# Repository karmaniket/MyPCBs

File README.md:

<h1 align="center">Explore my PCBs!!</h1>
<table>
  <tr>
    <td>
      <h3 align="center">Ldr sensor</h3>
      
    </td>
    <td>
      <h3 align="center">flip flop Led</h3>
      
    </td>
  </tr>
</table>

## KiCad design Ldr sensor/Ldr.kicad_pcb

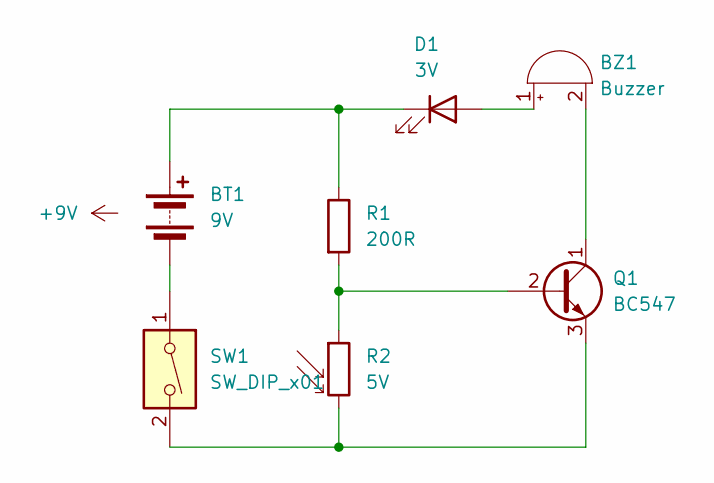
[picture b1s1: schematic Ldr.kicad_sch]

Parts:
BT1: 9V; Battery_connector
BZ1: Buzzer; Buzzer_12x9.5RM7.6
D1: 3V; LED_0805_2012Metric_Pad1.15x1.40mm_HandSolder
Q1: BC547; TO-92_Inline
R1: 200R; R_0805_2012Metric_Pad1.20x1.40mm_HandSolder
R2: 5V; R_LDR_10x8.5mm_P7.6mm_Vertical
SW1: SW_DIP_x01; SW_DIP_SPSTx01_Slide_6.7x4.1mm_W8.61mm_P2.54mm_LowProfile

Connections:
unnamed: BT1.1 (+), D1.1 (K), R1.1
unnamed: BT1.2 (-), SW1.1
unnamed: BZ1.2 (+), Q1.1 (C)
unnamed: BZ1.1 (-), D1.2 (A)
unnamed: Q1.2 (B), R1.2, R2.1
unnamed: Q1.3 (E), R2.2, SW1.2

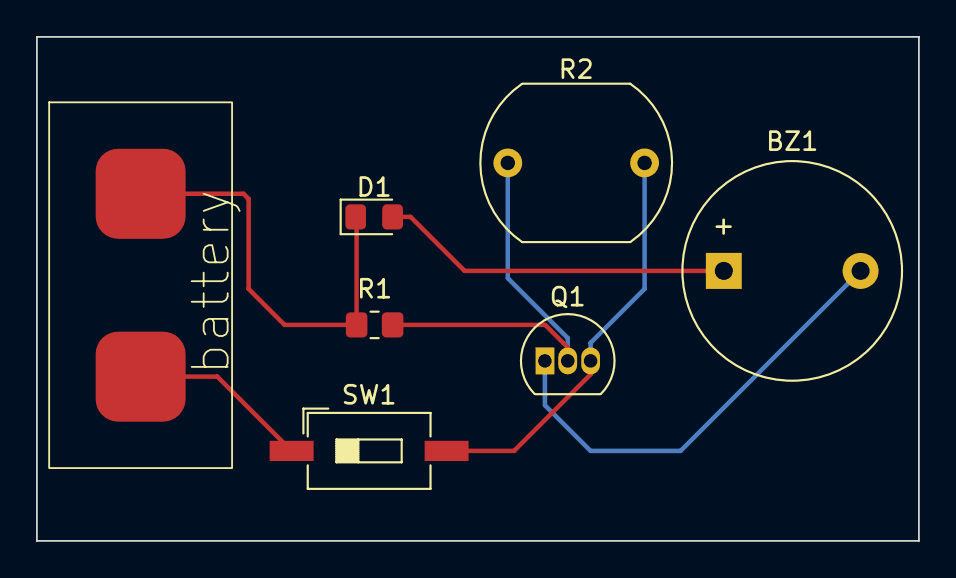
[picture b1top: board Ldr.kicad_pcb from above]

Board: 2 copper layers, 49.0 x 28.0 mm, 7 parts (0 on the bottom side), 6 nets.

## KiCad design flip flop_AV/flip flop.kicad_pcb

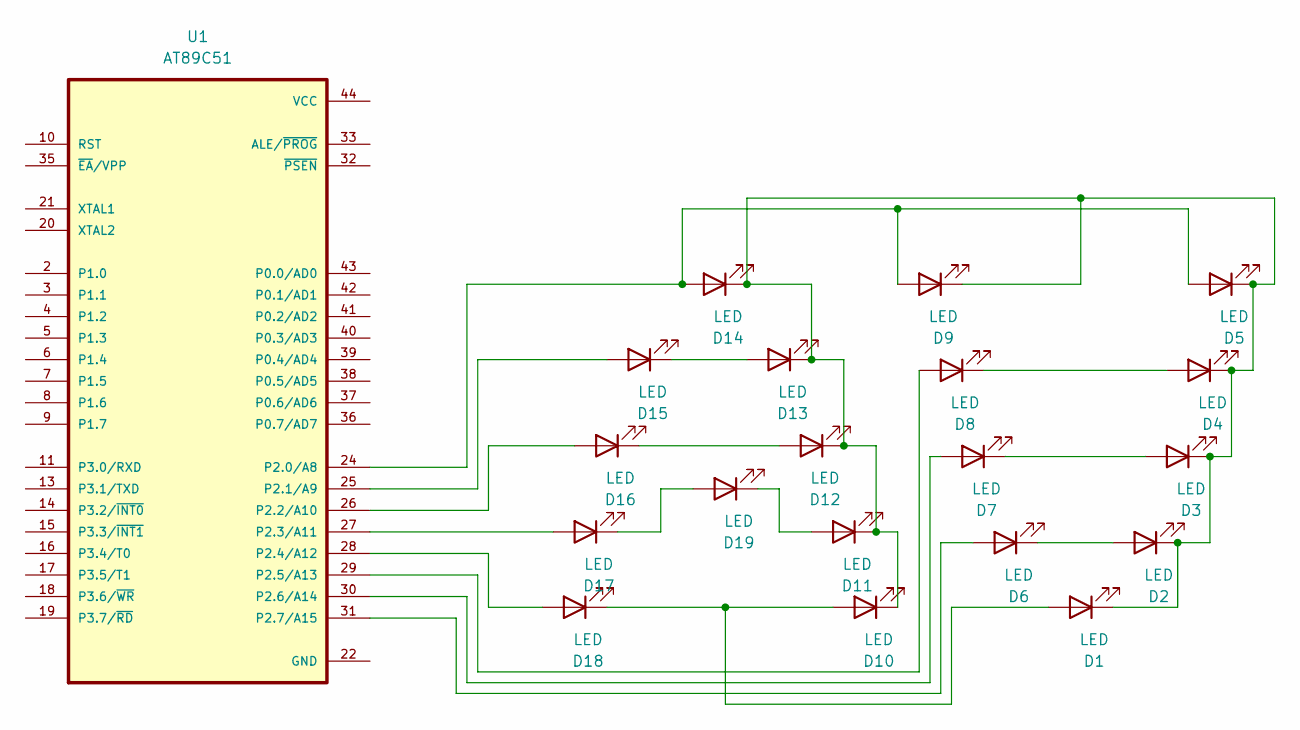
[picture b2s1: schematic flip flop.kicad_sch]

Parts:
D1, D2, D3, D4, D5, D6, D7, D8, D9, D10, D11, D12, D13, D14, D15, D16, D17, D18, D19: LED; LED_0805_2012Metric_Pad1.15x1.40mm_HandSolder
U1: AT89C51; PARTREV 0265G-02/00

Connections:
unnamed: D1.2 (A), D10.2 (A), D18.1 (K)
unnamed: D1.1 (K), D2.1 (K), D3.1 (K), D4.1 (K), D5.1 (K), D9.1 (K), D10.1 (K), D11.1 (K), D12.1 (K), D13.1 (K), D14.1 (K)
unnamed: D2.2 (A), D6.1 (K)
unnamed: D3.2 (A), D7.1 (K)
unnamed: D4.2 (A), D8.1 (K)
unnamed: D6.2 (A), U1.31 (P2.7/A15)
unnamed: D7.2 (A), U1.30 (P2.6/A14)
unnamed: D8.2 (A), U1.29 (P2.5/A13)
unnamed: D11.2 (A), D19.1 (K)
unnamed: D12.2 (A), D16.1 (K)
unnamed: D13.2 (A), D15.1 (K)
unnamed: D5.2 (A), D9.2 (A), D14.2 (A), U1.24 (P2.0/A8)
unnamed: D15.2 (A), U1.25 (P2.1/A9)
unnamed: D16.2 (A), U1.26 (P2.2/A10)
unnamed: D17.2 (A), U1.27 (P2.3/A11)
unnamed: D17.1 (K), D19.2 (A)
unnamed: D18.2 (A), U1.28 (P2.4/A12)

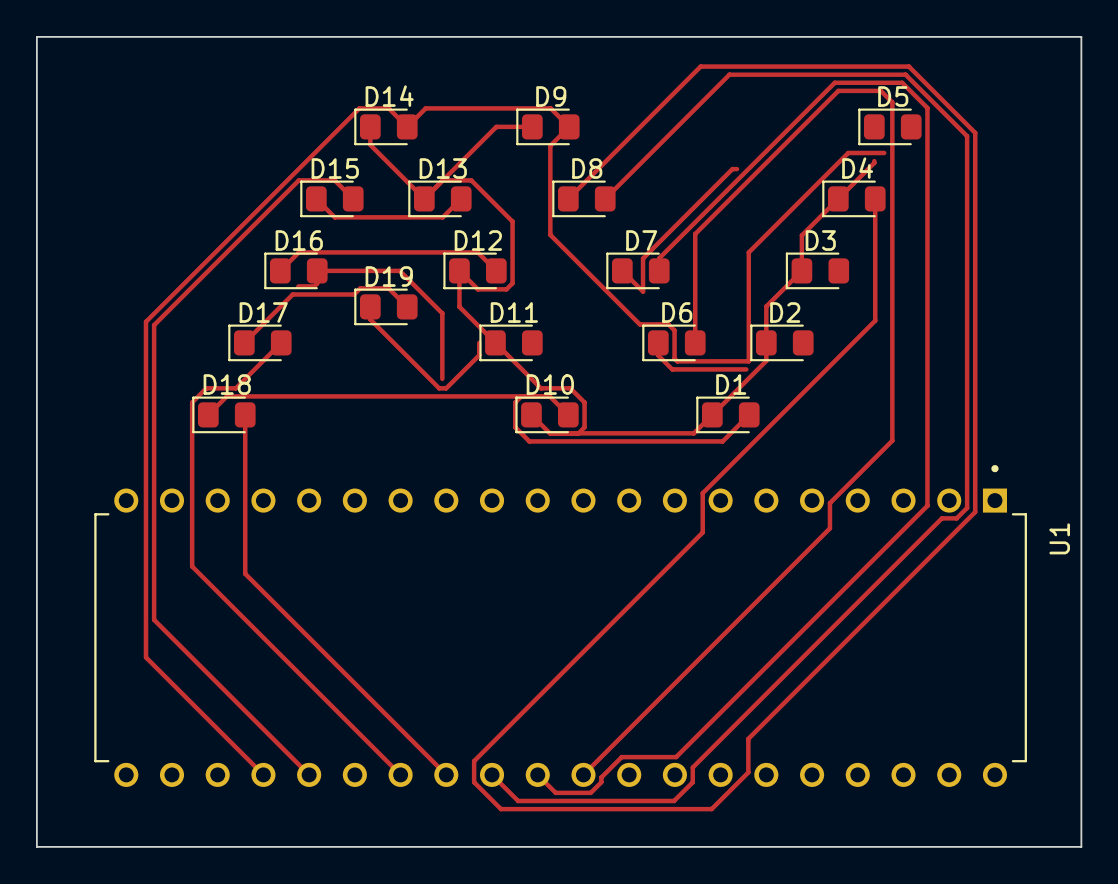
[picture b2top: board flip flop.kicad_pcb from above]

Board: 2 copper layers, 58.0 x 45.0 mm, 20 parts (0 on the bottom side), 17 nets.
